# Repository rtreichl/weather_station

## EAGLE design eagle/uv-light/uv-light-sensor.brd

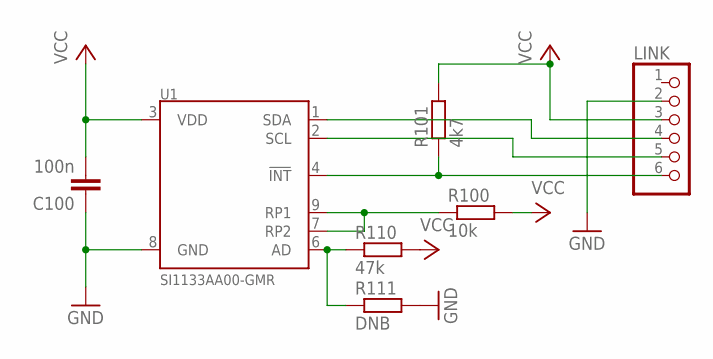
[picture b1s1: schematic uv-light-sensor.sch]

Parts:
C100: 100n; C0603
LINK: PINHD-1X6; 1X06
R100: 10k; R0603
R101: 4k7; R0603
R110: 47k; R0603
R111: DNB; R0603
U1: SI1133AA00-GMR; QFN-10/2MM

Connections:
GND: C100.1, LINK.2, R111.2, U1.8 (GND)
unnamed: LINK.6, R101.1, U1.4 (!INT)
unnamed: LINK.5, U1.2 (SCL)
unnamed: LINK.4, U1.1 (SDA)
unnamed: R100.1, U1.7 (RP2), U1.9 (RP1)
unnamed: R110.1, R111.1, U1.6 (AD)
VCC: C100.2, LINK.3, R100.2, R101.2, R110.2, U1.3 (VDD)

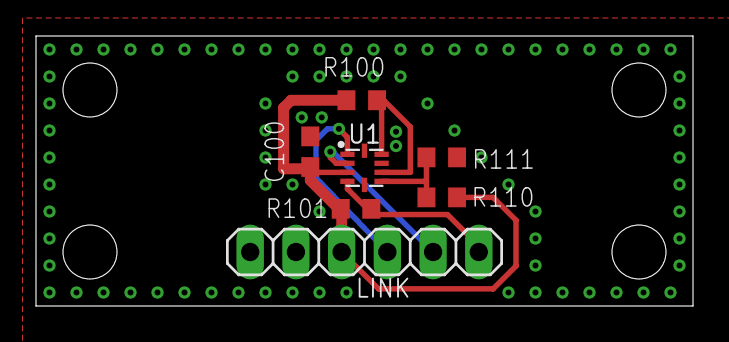
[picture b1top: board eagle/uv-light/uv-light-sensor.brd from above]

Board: 2 copper layers, 36.5 x 15.0 mm, 7 parts (0 on the bottom side), 7 nets.

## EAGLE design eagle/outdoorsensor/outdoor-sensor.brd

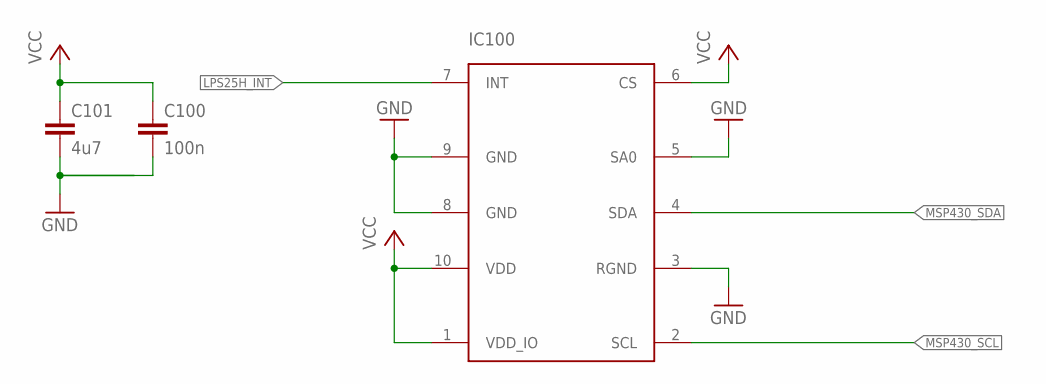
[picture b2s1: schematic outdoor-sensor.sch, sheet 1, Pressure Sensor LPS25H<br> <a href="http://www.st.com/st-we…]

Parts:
C100: 100n; C0603; MPN STP100NF04
C101: 4u7; C0603
IC100: LPS25H; MPN LPS25HBTR

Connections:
GND: C100.2, C101.2, IC100.3 (RGND), IC100.5 (SA0), IC100.8 (GND), IC100.9 (GND); also elsewhere on the board
LPS25H_INT: IC100.7 (INT); also elsewhere on the board
MSP430_SCL: IC100.2 (SCL); also elsewhere on the board
MSP430_SDA: IC100.4 (SDA); also elsewhere on the board
VCC: C100.1, C101.1, IC100.1 (VDD_IO), IC100.6 (CS), IC100.10 (VDD); also elsewhere on the board

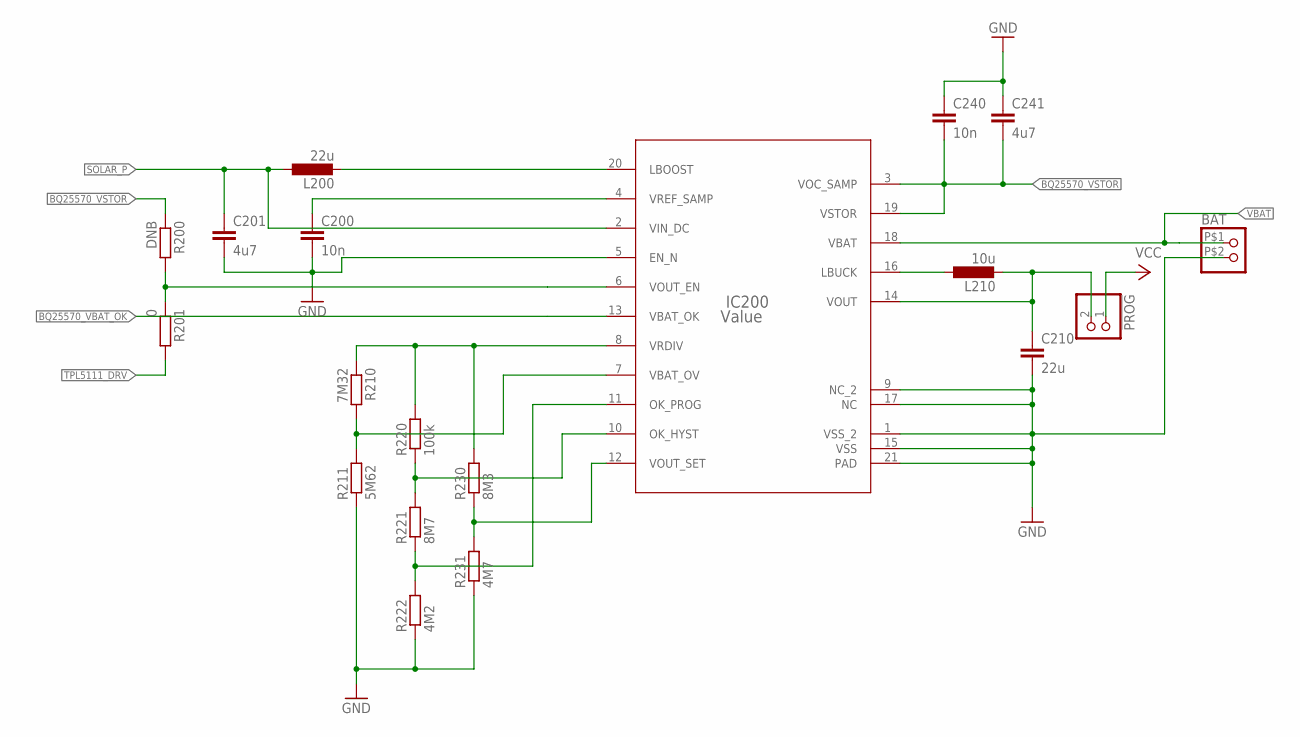
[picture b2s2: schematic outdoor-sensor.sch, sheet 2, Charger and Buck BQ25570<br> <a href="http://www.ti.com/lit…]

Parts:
!PROG: PINHD-1X2; 1X02
BAT: PINHD-1X2IPBS-102-01-T-S-GP; IPBS-102-01-T-S-GP
C200, C240: 10n; C0603
C201, C241: 4u7; C0603
C210: 22u; C0603; MPN 06034D226MAT2A
IC200: Value; RGR0020A
L200: 22u; L3944
L210: 10u; L2.5X2.0
R200: DNB; R0603
R201: 0; R0603
R210: 7M32; R0603
R211: 5M62; R0603
R220: 100k; R0603
R221: 8M7; R0603
R222: 4M2; R0603
R230: 8M3; R0603
R231: 4M7; R0603

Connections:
BQ25570_VBAT_OK: IC200.13 (VBAT_OK); also elsewhere on the board
BQ25570_VOUT_EN: IC200.6 (VOUT_EN), R200.2, R201.1
BQ25570_VSTOR: C240.2, C241.2, IC200.3 (VOC_SAMP), IC200.19 (VSTOR), R200.1; also elsewhere on the board
GND: BAT.P$2 (2), C200.2, C201.2, C210.2, C240.1, C241.1, IC200.1 (VSS_2), IC200.5 (EN_N), IC200.9 (NC_2), IC200.15 (VSS), IC200.17 (NC), IC200.21 (PAD), R211.1, R222.1, R231.1; also elsewhere on the board
unnamed: IC200.10 (OK_HYST), R220.1, R221.2
unnamed: IC200.8 (VRDIV), R210.1, R220.2, R230.2
unnamed: IC200.7 (VBAT_OV), R210.2, R211.2
unnamed: IC200.11 (OK_PROG), R221.1, R222.2
unnamed: IC200.20 (LBOOST), L200.P$2 (2)
unnamed: C200.1, IC200.4 (VREF_SAMP)
unnamed: IC200.12 (VOUT_SET), R230.1, R231.2
unnamed: !PROG.2, C210.1, IC200.14 (VOUT), L210.P$2 (2)
unnamed: IC200.16 (LBUCK), L210.P$1 (1)
SOLAR_P: C201.1, IC200.2 (VIN_DC), L200.P$1 (1); also elsewhere on the board
TPL5111_DRV: R201.2; also elsewhere on the board
VBAT: BAT.P$1 (1), IC200.18 (VBAT); also elsewhere on the board
VCC: !PROG.1; also elsewhere on the board

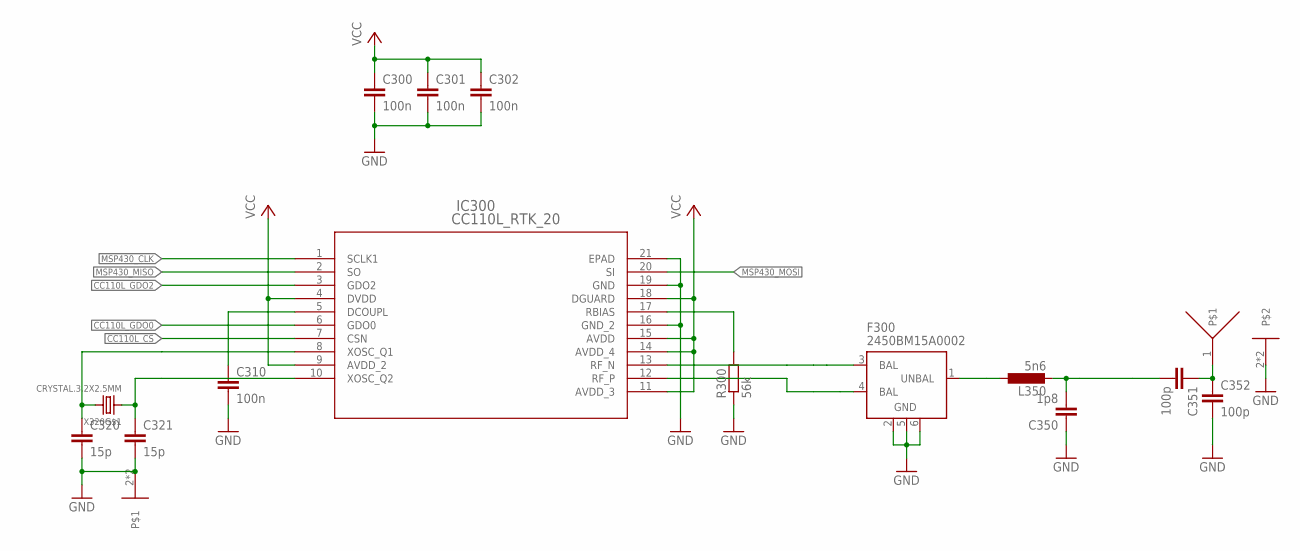
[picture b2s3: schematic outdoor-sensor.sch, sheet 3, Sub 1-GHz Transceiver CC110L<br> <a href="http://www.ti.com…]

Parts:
C300, C301, C302, C310: 100n; C0603; MPN STP100NF04
C320, C321: 15p; C0603
C350: 1p8; C0603K
C351: 100p; C0603
C352: 100p; C0603K
F300: 2450BM15A0002
IC300: CC110L_RTK_20; RTK20_2P4X2P4
L350: 5n6; L2012C
R300: 56k; R0603
U$1: ANTENNA868W3013-INV; W3013-INV
X320: CRYSTAL.3.2X2.5MM; 3.2X2.5MM

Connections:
!CC110L_CS: IC300.7 (CSN); also elsewhere on the board
CC110L_GDO0: IC300.6 (GDO0); also elsewhere on the board
CC110L_GDO2: IC300.3 (GDO2); also elsewhere on the board
GND: C300.2, C301.2, C302.2, C310.2, C320.2, C321.2, C350.1, C352.2, F300.2 (GND), F300.5 (GND), F300.6 (GND), IC300.16 (GND_2), IC300.19 (GND), IC300.21 (EPAD), R300.1, U$1.2, U$1.3, X320.2, X320.4; also elsewhere on the board
MSP430_CLK: IC300.1 (SCLK1); also elsewhere on the board
MSP430_MISO: IC300.2 (SO); also elsewhere on the board
MSP430_MOSI: IC300.20 (SI); also elsewhere on the board
unnamed: C351.1, C352.1, U$1.1
unnamed: F300.1 (UNBAL), L350.1
unnamed: C320.1, IC300.8 (XOSC_Q1), X320.3 (2)
unnamed: F300.3 (BAL), IC300.13 (RF_N)
unnamed: F300.4 (BAL), IC300.12 (RF_P)
unnamed: C350.2, C351.2, L350.2
unnamed: C310.1, IC300.5 (DCOUPL)
unnamed: IC300.17 (RBIAS), R300.2
unnamed: C321.1, IC300.10 (XOSC_Q2), X320.1
VCC: C300.1, C301.1, C302.1, IC300.4 (DVDD), IC300.9 (AVDD_2), IC300.11 (AVDD_3), IC300.14 (AVDD_4), IC300.15 (AVDD), IC300.18 (DGUARD); also elsewhere on the board

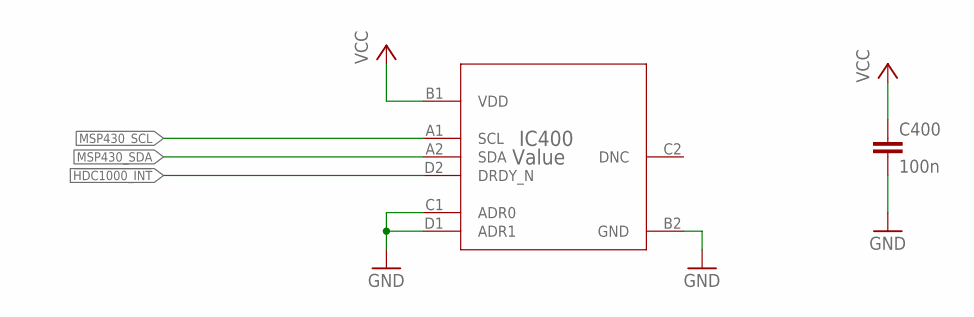
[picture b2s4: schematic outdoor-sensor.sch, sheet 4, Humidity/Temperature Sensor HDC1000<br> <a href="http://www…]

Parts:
C400: 100n; C0603; MPN STP100NF04
IC400: Value; YPA0008AGAE

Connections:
!HDC1000_INT: IC400.D2 (DRDY_N); also elsewhere on the board
GND: C400.2, IC400.B2 (GND), IC400.C1 (ADR0), IC400.D1 (ADR1); also elsewhere on the board
MSP430_SCL: IC400.A1 (SCL); also elsewhere on the board
MSP430_SDA: IC400.A2 (SDA); also elsewhere on the board
VCC: C400.1, IC400.B1 (VDD); also elsewhere on the board

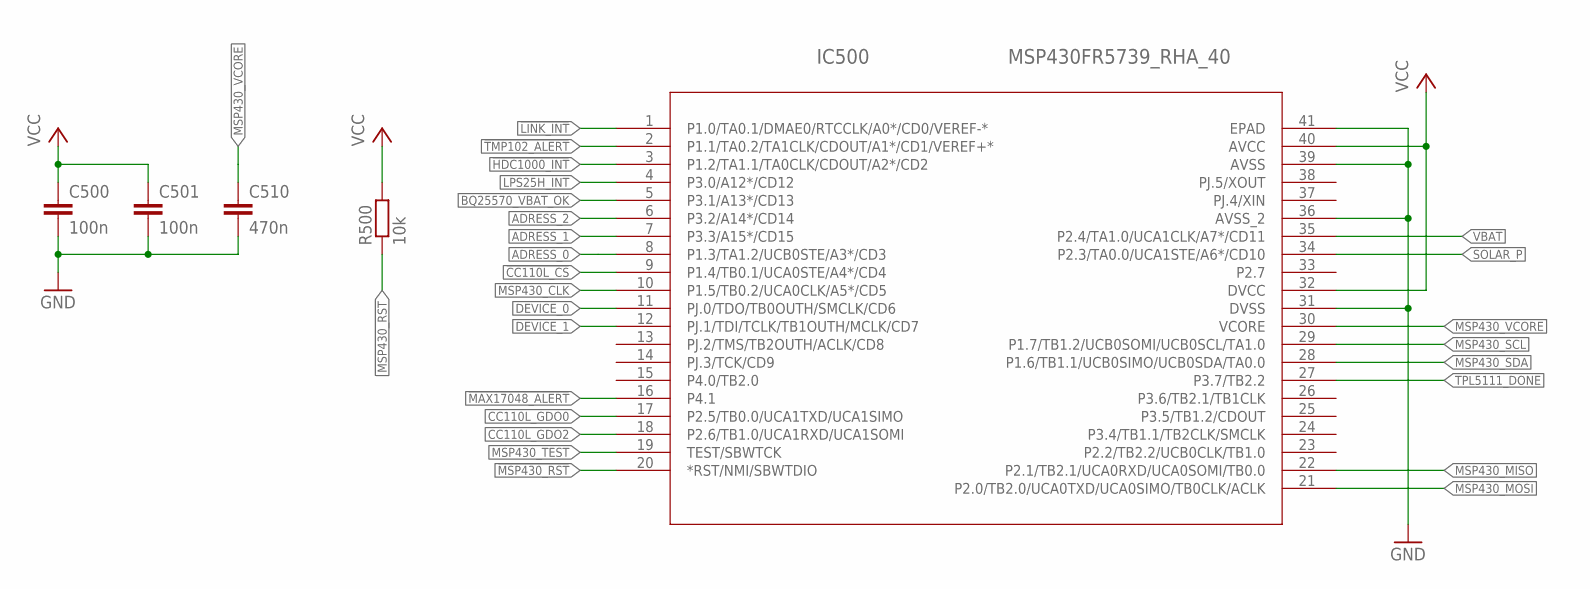
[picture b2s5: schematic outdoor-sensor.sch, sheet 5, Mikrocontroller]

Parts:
C500, C501: 100n; C0603; MPN STP100NF04
C510: 470n; C0603
IC500: MSP430FR5739_RHA_40; RHA40_2P9X2P9
R500: 10k; R0603

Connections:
!CC110L_CS: IC500.9 (P1.4/TB0.1/UCA0STE/A4*/CD4); also elsewhere on the board
!HDC1000_INT: IC500.3 (P1.2/TA1.1/TA0CLK/CDOUT/A2*/CD2); also elsewhere on the board
!LINK_INT: IC500.1 (P1.0/TA0.1/DMAE0/RTCCLK/A0*/CD0/VEREF-*); also elsewhere on the board
!MAX17048_ALERT: IC500.16 (P4.1); also elsewhere on the board
!MSP430_RST: IC500.20 (*RST/NMI/SBWTDIO), R500.1; also elsewhere on the board
!TMP102_ALERT: IC500.2 (P1.1/TA0.2/TA1CLK/CDOUT/A1*/CD1/VEREF+*); also elsewhere on the board
ADRESS_0: IC500.8 (P1.3/TA1.2/UCB0STE/A3*/CD3); also elsewhere on the board
ADRESS_1: IC500.7 (P3.3/A15*/CD15); also elsewhere on the board
ADRESS_2: IC500.6 (P3.2/A14*/CD14); also elsewhere on the board
BQ25570_VBAT_OK: IC500.5 (P3.1/A13*/CD13); also elsewhere on the board
CC110L_GDO0: IC500.17 (P2.5/TB0.0/UCA1TXD/UCA1SIMO); also elsewhere on the board
CC110L_GDO2: IC500.18 (P2.6/TB1.0/UCA1RXD/UCA1SOMI); also elsewhere on the board
DEVICE_0: IC500.11 (PJ.0/TDO/TB0OUTH/SMCLK/CD6); also elsewhere on the board
DEVICE_1: IC500.12 (PJ.1/TDI/TCLK/TB1OUTH/MCLK/CD7); also elsewhere on the board
GND: C500.2, C501.2, C510.2, IC500.31 (DVSS), IC500.36 (AVSS_2), IC500.39 (AVSS), IC500.41 (EPAD); also elsewhere on the board
LPS25H_INT: IC500.4 (P3.0/A12*/CD12); also elsewhere on the board
MSP430_CLK: IC500.10 (P1.5/TB0.2/UCA0CLK/A5*/CD5); also elsewhere on the board
MSP430_MISO: IC500.22 (P2.1/TB2.1/UCA0RXD/UCA0SOMI/TB0.0); also elsewhere on the board
MSP430_MOSI: IC500.21 (P2.0/TB2.0/UCA0TXD/UCA0SIMO/TB0CLK/ACLK); also elsewhere on the board
MSP430_SCL: IC500.29 (P1.7/TB1.2/UCB0SOMI/UCB0SCL/TA1.0); also elsewhere on the board
MSP430_SDA: IC500.28 (P1.6/TB1.1/UCB0SIMO/UCB0SDA/TA0.0); also elsewhere on the board
MSP430_TEST: IC500.19 (TEST/SBWTCK); also elsewhere on the board
MSP430_VCORE: C510.1, IC500.30 (VCORE)
SOLAR_P: IC500.34 (P2.3/TA0.0/UCA1STE/A6*/CD10); also elsewhere on the board
TPL5111_DONE: IC500.27 (P3.7/TB2.2); also elsewhere on the board
VBAT: IC500.35 (P2.4/TA1.0/UCA1CLK/A7*/CD11); also elsewhere on the board
VCC: C500.1, C501.1, IC500.32 (DVCC), IC500.40 (AVCC), R500.2; also elsewhere on the board

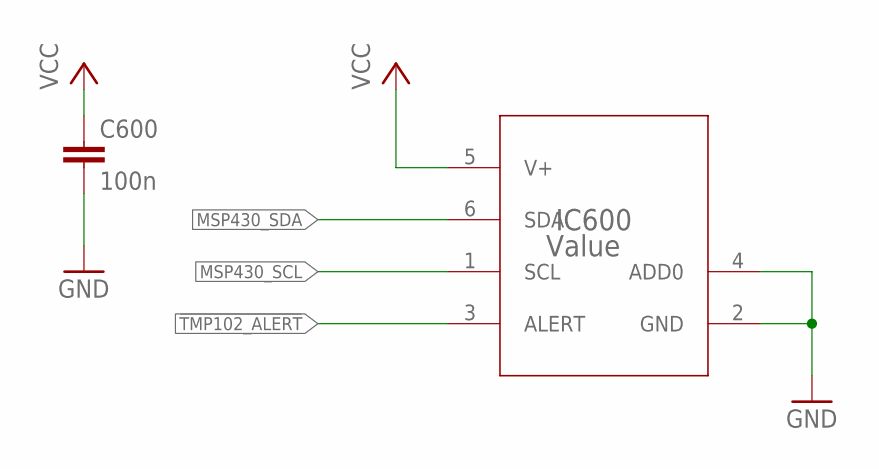
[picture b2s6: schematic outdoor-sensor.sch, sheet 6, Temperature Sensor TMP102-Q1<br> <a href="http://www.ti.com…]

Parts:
C600: 100n; C0603; MPN STP100NF04
IC600: Value; DRL0006A

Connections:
!TMP102_ALERT: IC600.3 (ALERT); also elsewhere on the board
GND: C600.2, IC600.2 (GND), IC600.4 (ADD0); also elsewhere on the board
MSP430_SCL: IC600.1 (SCL); also elsewhere on the board
MSP430_SDA: IC600.6 (SDA); also elsewhere on the board
VCC: C600.1, IC600.5 (V+); also elsewhere on the board

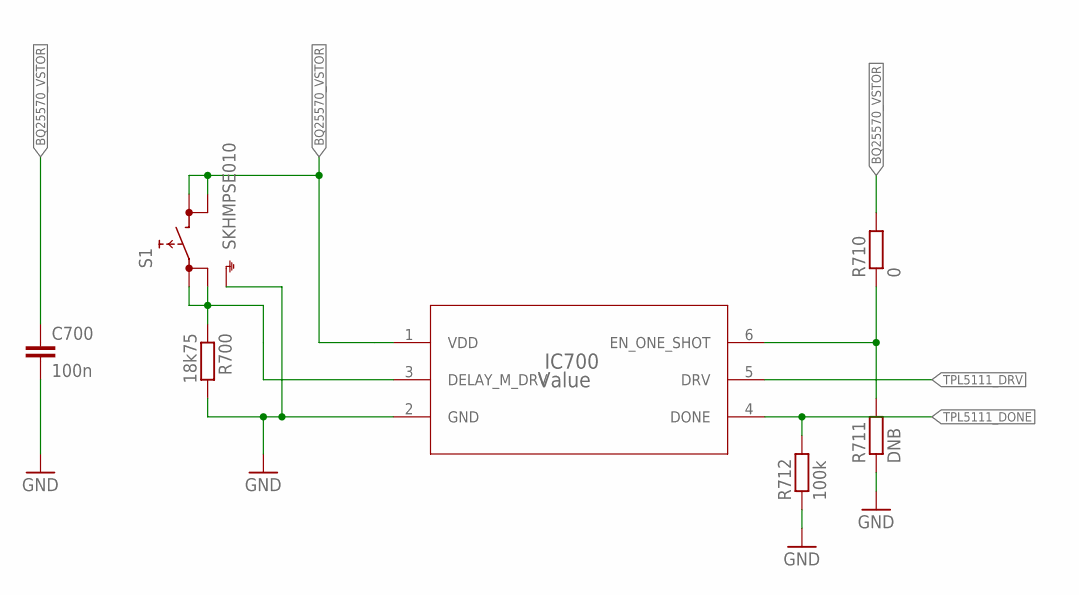
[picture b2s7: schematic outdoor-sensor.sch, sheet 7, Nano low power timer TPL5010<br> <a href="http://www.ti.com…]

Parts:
C700: 100n; C0603; MPN STP100NF04
IC700: Value; DDC0006A_N
R700: 18k75; R0603
R710: 0; R0603
R711: DNB; R0603
R712: 100k; R0603
S1: SKHMPSE010; SKHMPXE010

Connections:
BQ25570_VSTOR: C700.1, IC700.1 (VDD), R710.2, S1.3 (2.1), S1.4 (2.2); also elsewhere on the board
GND: C700.2, IC700.2 (GND), R700.2, R711.1, R712.1, S1.5 (SH); also elsewhere on the board
unnamed: IC700.3 (DELAY_M_DRV), R700.1, S1.1 (1.1), S1.2 (1.2)
TPL5010_RST_N: IC700.6 (EN_ONE_SHOT), R710.1, R711.2
TPL5111_DONE: IC700.4 (DONE), R712.2; also elsewhere on the board
TPL5111_DRV: IC700.5 (DRV); also elsewhere on the board

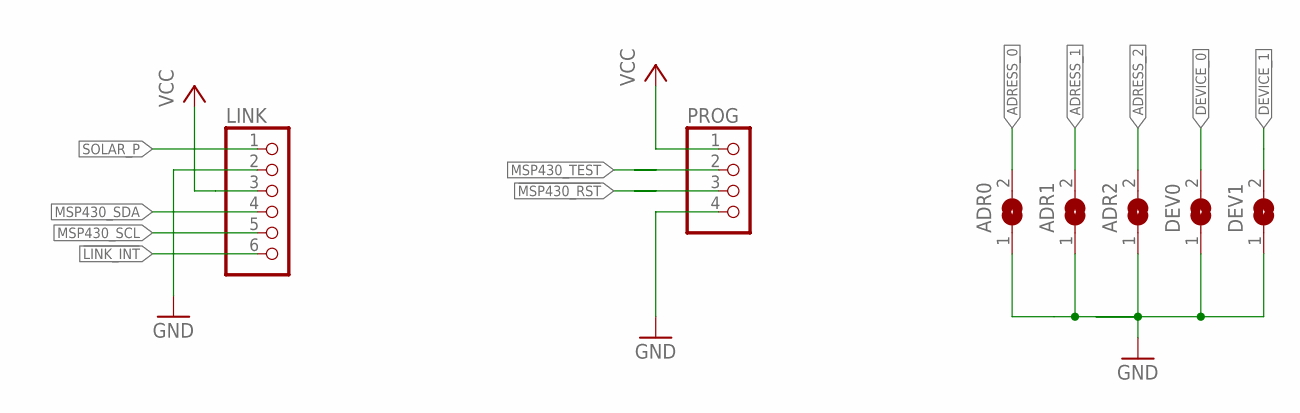
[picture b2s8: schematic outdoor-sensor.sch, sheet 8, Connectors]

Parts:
ADR0, ADR1, ADR2: SJW
DEV0, DEV1: SJW
LINK: PINHD-1X6; 1X06
PROG: PINHD-1X4; 1X04

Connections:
!LINK_INT: LINK.6; also elsewhere on the board
!MSP430_RST: PROG.3; also elsewhere on the board
ADRESS_0: ADR0.2; also elsewhere on the board
ADRESS_1: ADR1.2; also elsewhere on the board
ADRESS_2: ADR2.2; also elsewhere on the board
DEVICE_0: DEV0.2; also elsewhere on the board
DEVICE_1: DEV1.2; also elsewhere on the board
GND: ADR0.1, ADR1.1, ADR2.1, DEV0.1, DEV1.1, LINK.2, PROG.4; also elsewhere on the board
MSP430_SCL: LINK.5; also elsewhere on the board
MSP430_SDA: LINK.4; also elsewhere on the board
MSP430_TEST: PROG.2; also elsewhere on the board
SOLAR_P: LINK.1; also elsewhere on the board
VCC: LINK.3, PROG.1; also elsewhere on the board

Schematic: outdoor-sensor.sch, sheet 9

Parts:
C800: 100n; C0603
IC800: MAX17048X+; 21-0555B_W80B1-1

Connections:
!MAX17048_ALERT: IC800.B4 (*ALRT); also elsewhere on the board
GND: C800.2, IC800.A1 (CTG), IC800.A4 (GND), IC800.B3 (QSTRT); also elsewhere on the board
MSP430_SCL: IC800.B2 (SCL); also elsewhere on the board
MSP430_SDA: IC800.B1 (SDA); also elsewhere on the board
VBAT: C800.1, IC800.A2 (CELL), IC800.A3 (VDD); also elsewhere on the board

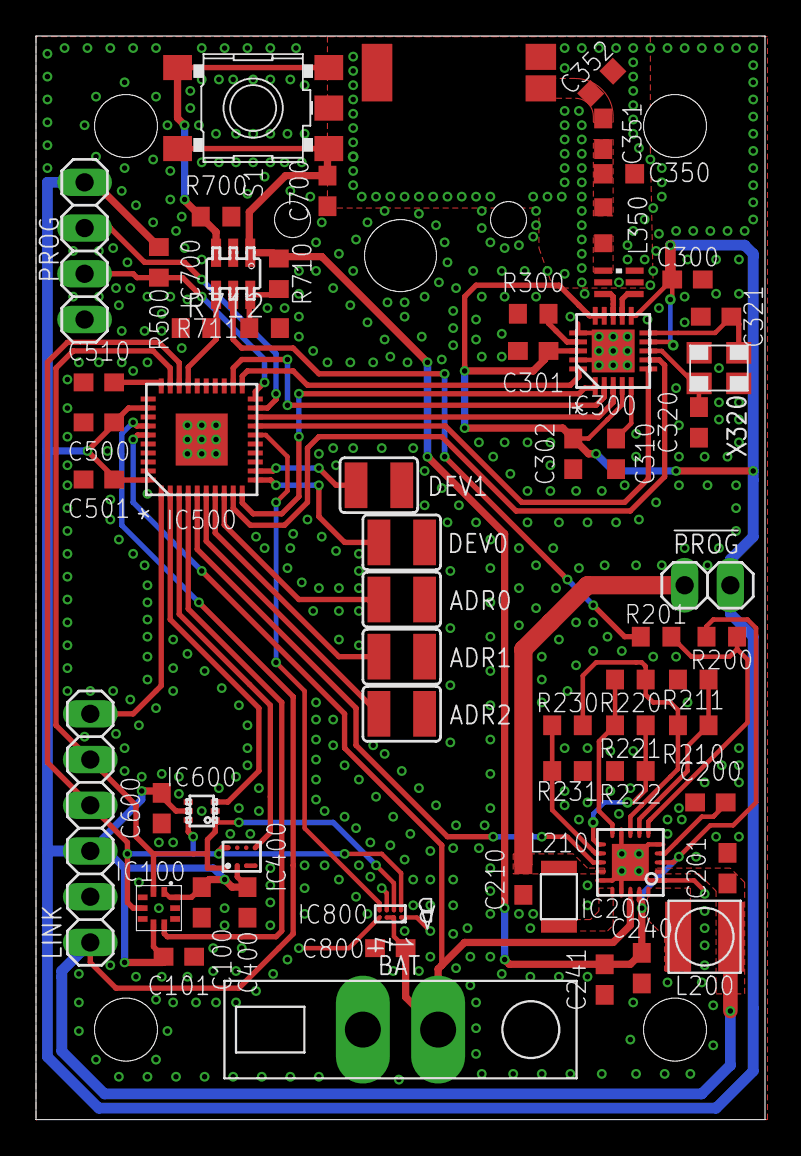
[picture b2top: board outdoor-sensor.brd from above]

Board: 2 copper layers, 40.5 x 60.2 mm, 62 parts (0 on the bottom side), 50 nets.

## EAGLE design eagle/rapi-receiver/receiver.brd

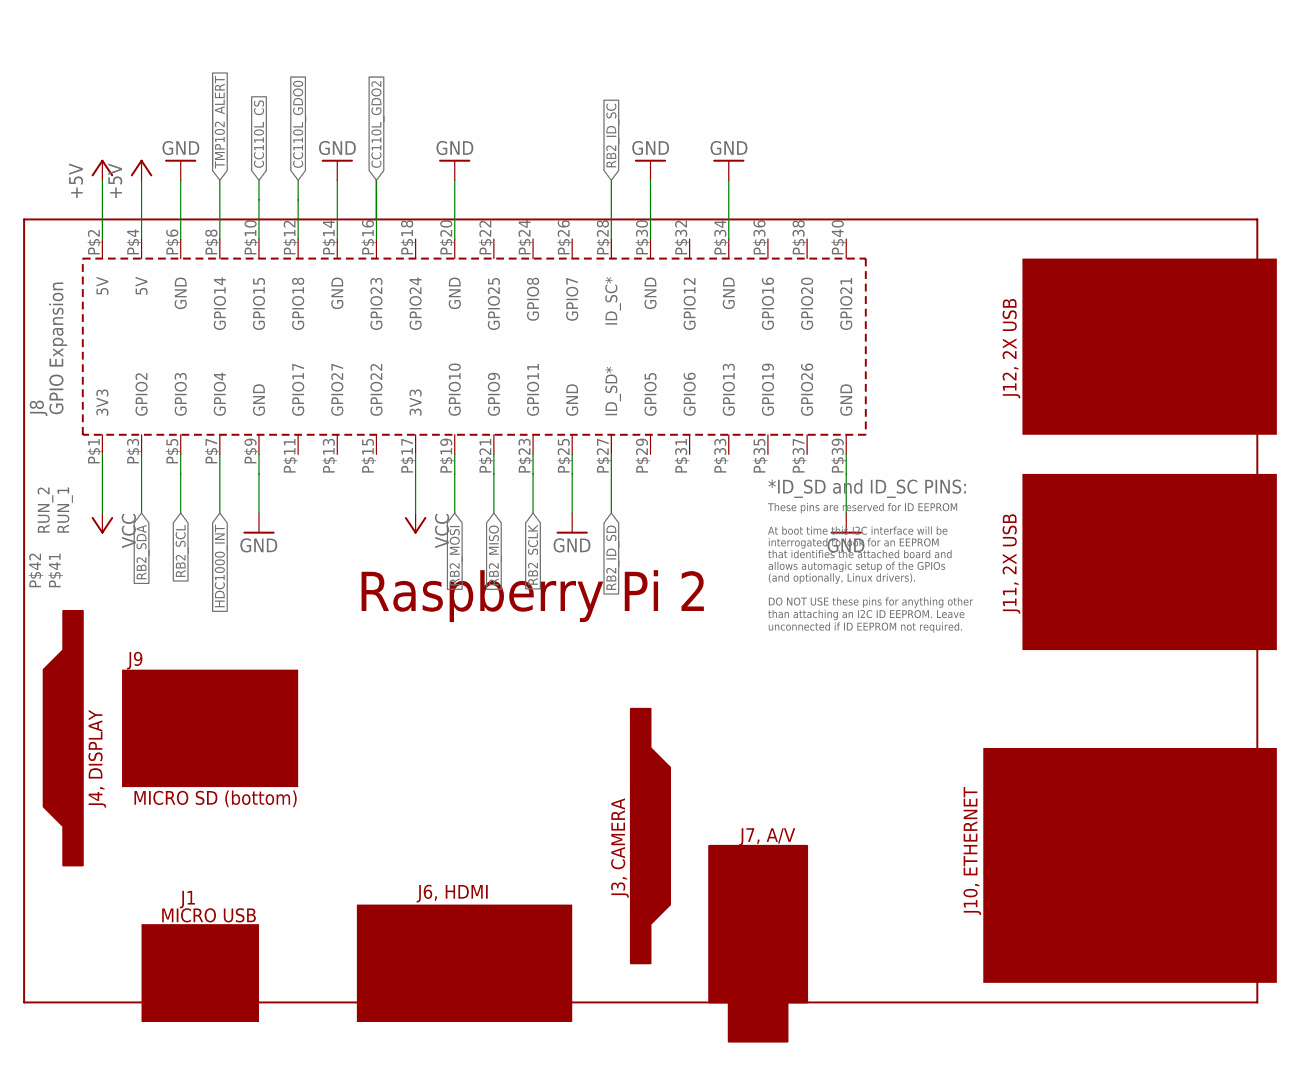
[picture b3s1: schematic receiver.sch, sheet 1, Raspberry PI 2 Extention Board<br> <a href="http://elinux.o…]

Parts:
PCB1: RPI2

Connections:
!HDC1000_INT: PCB1.P$7 (GPIO4); also elsewhere on the board
!TMP102_ALERT: PCB1.P$8 (GPIO14); also elsewhere on the board
+5V: PCB1.P$2 (5V), PCB1.P$4 (5V)
CC110L_CS: PCB1.P$10 (GPIO15); also elsewhere on the board
CC110L_GDO0: PCB1.P$12 (GPIO18); also elsewhere on the board
CC110L_GDO2: PCB1.P$16 (GPIO23); also elsewhere on the board
GND: PCB1.P$6 (GND), PCB1.P$9 (GND), PCB1.P$14 (GND), PCB1.P$20 (GND), PCB1.P$25 (GND), PCB1.P$30 (GND), PCB1.P$34 (GND), PCB1.P$39 (GND); also elsewhere on the board
RB2_ID_SC: PCB1.P$28 (ID_SC*); also elsewhere on the board
RB2_ID_SD: PCB1.P$27 (ID_SD*); also elsewhere on the board
RB2_MISO: PCB1.P$21 (GPIO9); also elsewhere on the board
RB2_MOSI: PCB1.P$19 (GPIO10); also elsewhere on the board
RB2_SCL: PCB1.P$5 (GPIO3); also elsewhere on the board
RB2_SCLK: PCB1.P$23 (GPIO11); also elsewhere on the board
RB2_SDA: PCB1.P$3 (GPIO2); also elsewhere on the board
VCC: PCB1.P$1 (3V3), PCB1.P$17 (3V3); also elsewhere on the board

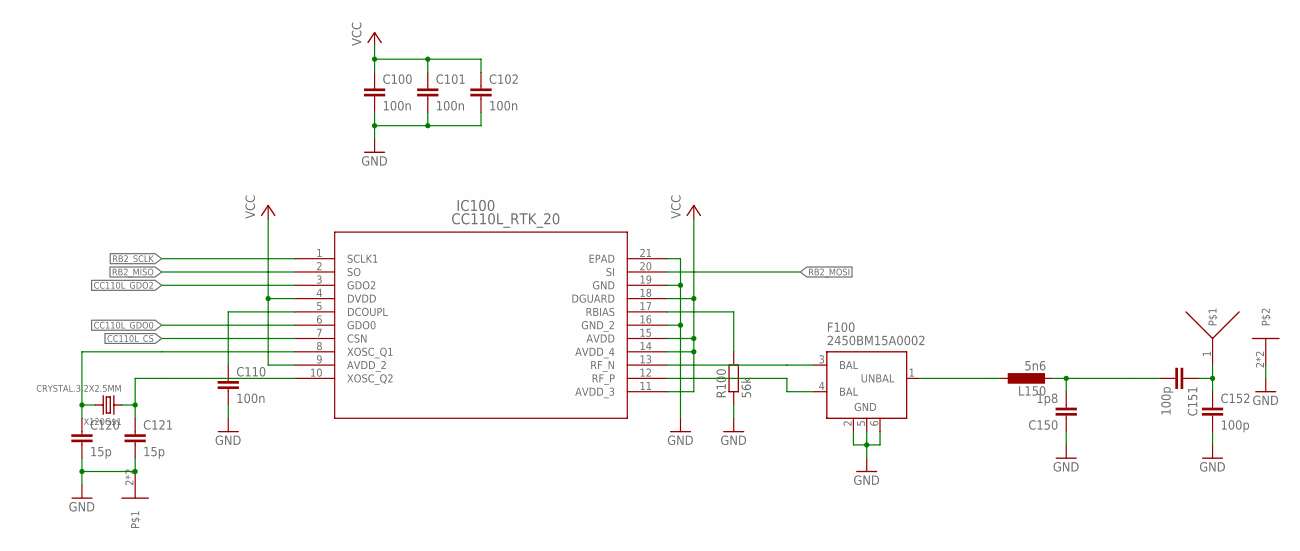
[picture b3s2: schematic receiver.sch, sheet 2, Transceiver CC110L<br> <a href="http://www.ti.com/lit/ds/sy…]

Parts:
C100, C101, C102, C110: 100n; C0603
C120, C121: 15p; C0603
C150: 1p8; C0603K
C151: 100p; C0603
C152: 100p; C0603K
F100: 2450BM15A0002
IC100: CC110L_RTK_20; RTK20_2P4X2P4
L150: 5n6; L2012C
R100: 56k; R0603
U$1: ANTENNA868W3013-INV; W3013-INV
X120: CRYSTAL.3.2X2.5MM; 3.2X2.5MM

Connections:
CC110L_CS: IC100.7 (CSN); also elsewhere on the board
CC110L_GDO0: IC100.6 (GDO0); also elsewhere on the board
CC110L_GDO2: IC100.3 (GDO2); also elsewhere on the board
GND: C100.2, C101.2, C102.2, C110.2, C120.2, C121.2, C150.1, C152.2, F100.2 (GND), F100.5 (GND), F100.6 (GND), IC100.16 (GND_2), IC100.19 (GND), IC100.21 (EPAD), R100.1, U$1.2, U$1.3, X120.2, X120.4; also elsewhere on the board
unnamed: C151.1, C152.1, U$1.1
unnamed: C120.1, IC100.8 (XOSC_Q1), X120.3 (2)
unnamed: F100.1 (UNBAL), L150.1
unnamed: F100.3 (BAL), IC100.13 (RF_N)
unnamed: F100.4 (BAL), IC100.12 (RF_P)
unnamed: C150.2, C151.2, L150.2
unnamed: C110.1, IC100.5 (DCOUPL)
unnamed: IC100.17 (RBIAS), R100.2
unnamed: C121.1, IC100.10 (XOSC_Q2), X120.1
RB2_MISO: IC100.2 (SO); also elsewhere on the board
RB2_MOSI: IC100.20 (SI); also elsewhere on the board
RB2_SCLK: IC100.1 (SCLK1); also elsewhere on the board
VCC: C100.1, C101.1, C102.1, IC100.4 (DVDD), IC100.9 (AVDD_2), IC100.11 (AVDD_3), IC100.14 (AVDD_4), IC100.15 (AVDD), IC100.18 (DGUARD); also elsewhere on the board

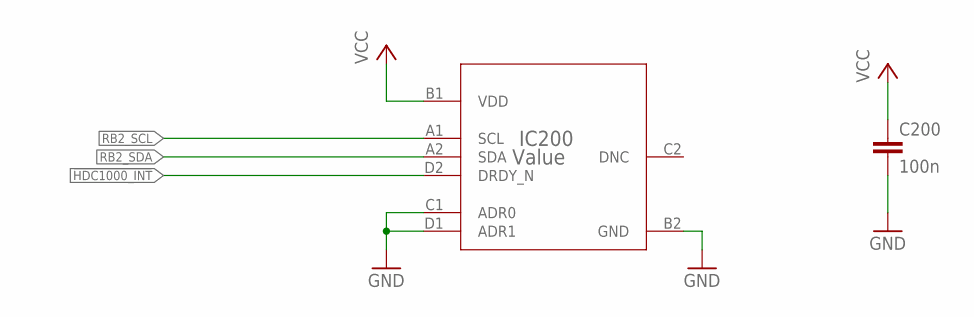
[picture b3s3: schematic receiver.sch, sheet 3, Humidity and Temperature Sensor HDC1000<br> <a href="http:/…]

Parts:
C200: 100n; C0603
IC200: Value; YPA0008AGAE

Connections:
!HDC1000_INT: IC200.D2 (DRDY_N); also elsewhere on the board
GND: C200.2, IC200.B2 (GND), IC200.C1 (ADR0), IC200.D1 (ADR1); also elsewhere on the board
RB2_SCL: IC200.A1 (SCL); also elsewhere on the board
RB2_SDA: IC200.A2 (SDA); also elsewhere on the board
VCC: C200.1, IC200.B1 (VDD); also elsewhere on the board

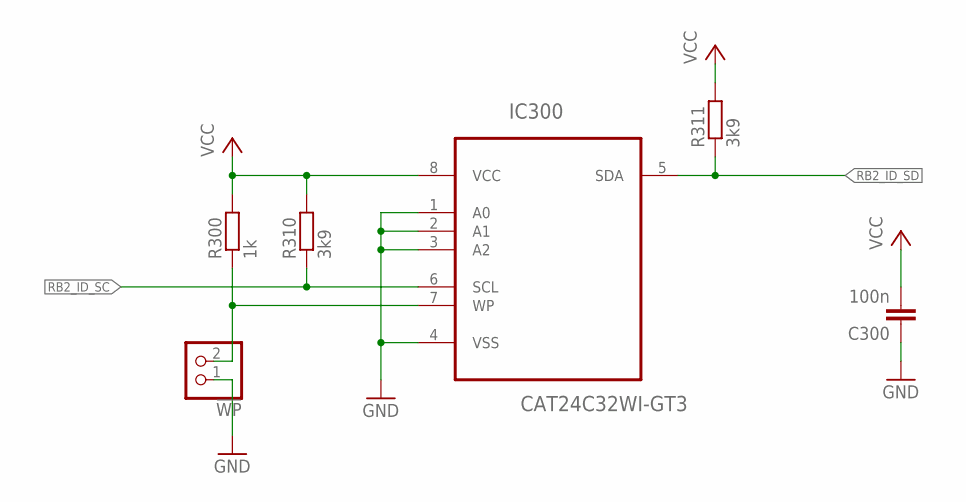
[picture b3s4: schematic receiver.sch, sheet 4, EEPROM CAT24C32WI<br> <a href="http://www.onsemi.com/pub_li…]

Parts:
!WP: PINHD-1X2; 1X02
C300: 100n; C0603
IC300: CAT24C32WI-GT3; SOIC127P600X175-8N
R300: 1k; R0603
R310, R311: 3k9; R0603

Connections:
GND: !WP.1, C300.1, IC300.1 (A0), IC300.2 (A1), IC300.3 (A2), IC300.4 (VSS); also elsewhere on the board
unnamed: !WP.2, IC300.7 (WP), R300.1
RB2_ID_SC: IC300.6 (SCL), R310.1; also elsewhere on the board
RB2_ID_SD: IC300.5 (SDA), R311.1; also elsewhere on the board
VCC: C300.2, IC300.8 (VCC), R300.2, R310.2, R311.2; also elsewhere on the board

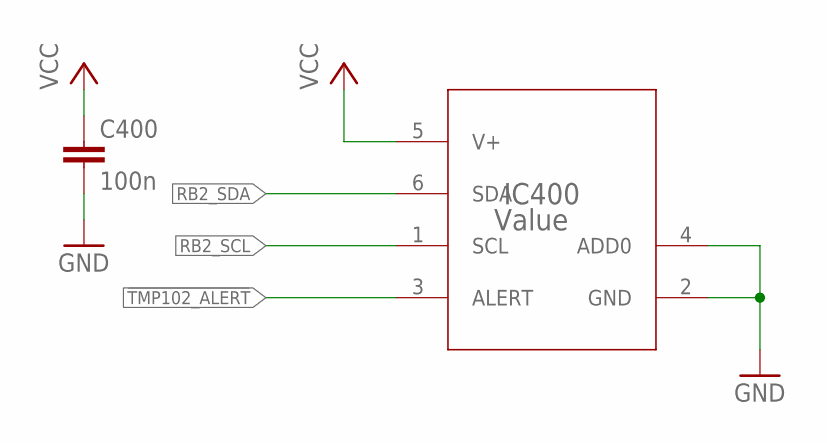
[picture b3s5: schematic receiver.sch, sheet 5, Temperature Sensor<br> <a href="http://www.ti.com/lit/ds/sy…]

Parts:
C400: 100n; C0603
IC400: Value; DRL0006A

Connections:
!TMP102_ALERT: IC400.3 (ALERT); also elsewhere on the board
GND: C400.2, IC400.2 (GND), IC400.4 (ADD0); also elsewhere on the board
RB2_SCL: IC400.1 (SCL); also elsewhere on the board
RB2_SDA: IC400.6 (SDA); also elsewhere on the board
VCC: C400.1, IC400.5 (V+); also elsewhere on the board

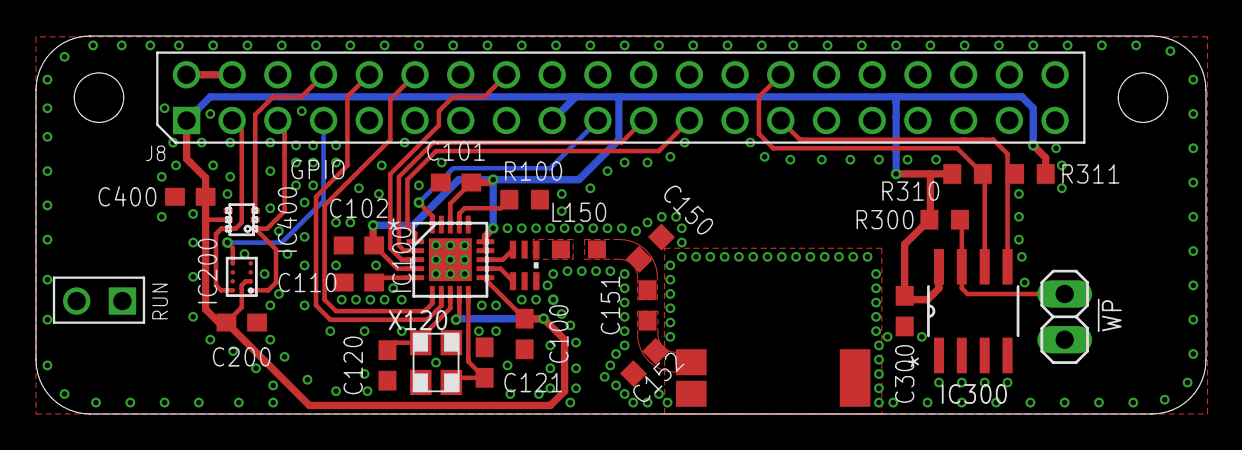
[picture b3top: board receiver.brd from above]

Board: 2 copper layers, 65.0 x 21.0 mm, 26 parts (0 on the bottom side), 25 nets.

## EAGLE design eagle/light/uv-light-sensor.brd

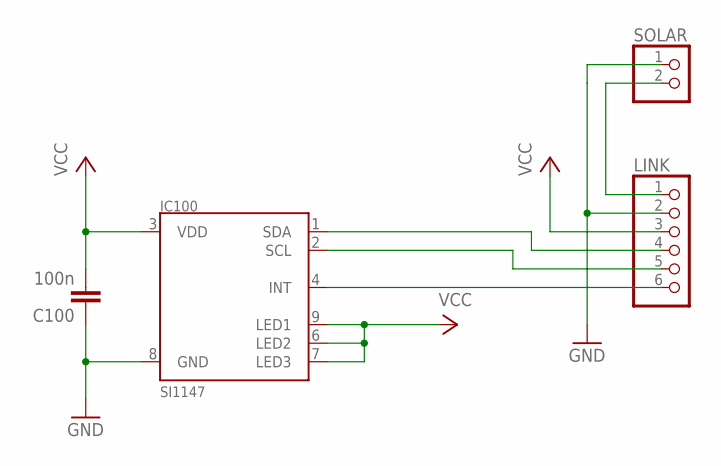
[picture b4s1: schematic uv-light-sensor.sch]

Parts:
C100: 100n; C0603
IC100: SI1147; QFN-10/2MM
LINK: PINHD-1X6; 1X06
SOLAR: PINHD-1X2; 1X02

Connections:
GND: C100.1, IC100.8 (GND), LINK.2, SOLAR.1
unnamed: IC100.4 (INT), LINK.6
unnamed: IC100.2 (SCL), LINK.5
unnamed: IC100.1 (SDA), LINK.4
unnamed: LINK.1, SOLAR.2
VCC: C100.2, IC100.3 (VDD), IC100.6 (LED2), IC100.7 (LED3), IC100.9 (LED1), LINK.3

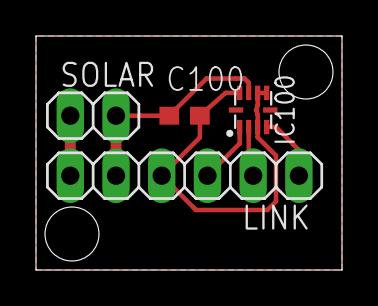
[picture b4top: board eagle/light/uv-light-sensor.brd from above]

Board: 2 copper layers, 17.0 x 13.0 mm, 4 parts (0 on the bottom side), 6 nets.

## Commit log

2015-07-07 Init: Initial commint with needed folder structur
2015-08-13 ADD: Schematics and layout for outdoor light sensor and receiver for raspberry pi 2
2015-10-21 ADD: first C-Project of transmitter
2015-10-21 CHG: updated lib, schematics and boards
2016-01-28 RM: Deleted old Prject
2016-01-28 ADD: New project for OutdoorSensor
    actually state is working
2016-01-28 CHG: Updated schematics and layout
2016-01-28 ADD: New project for Receiver on Raspbery Pi2
2016-01-28 CHG: Several changes due to new protocol
2016-01-28 CHG: added factors for conversion of raw data to real data
2016-01-28 CHG: restructed mysql commands due to protcocl changes
2016-01-28 CHG: Some structur improvments
2016-02-17 CHG: Removed extern_interrupt_handler and replaced with with new gpio interface
2016-02-17 CHG: Added new timer interface
2016-02-17 CHG: Updated some MYSQL strings
2016-02-17 CHG: reworked database data handling and added rssi for database insert
2016-02-17 FIX: fixed some bugs on cc110l driver
2016-02-18 ADD: added clock interface
2016-02-26 ADD: Added a Systemtimer function, also moved system relevant files to a own folder on the lib path renamed some macros and function due to new folder structure
2016-02-26 FIX: Moved config from ram to rom
2016-02-26 ADD: added a onewire driver. Port and Pin are selectable
2016-02-26 CHG: Improved timer driver and fixed some bugs
2016-02-26 ADD: Added an check slave function to i2c for checking availability
2016-02-26 ADD: Added driver for DS18B20 Temp. sensor
2016-02-26 FIX: fixed a bug with GPIO ISR
2016-02-26 CHG: Added library to include pathes, and cleaned up main due to fewer changes
2016-02-26 ADD: Added files for driver lib. Driver lib will be moved out of this repo. to a independently one
2016-02-29 CHG: Moved files in new directory and changed code for new structure
2016-02-29 ADD: added a i2c_slave_check function to prove if the slave exists
2016-02-29 CHG: tmp102 changed converstion rate from 1s to 125ms and added a wait statement for it
2016-02-29 CHG: Splitted PA-Table marco in to different macros
2016-02-29 ADD: added a start up wait condition for the hdc1000
2016-02-29 ADD: added a start up wait condition for the si1147
2016-02-29 ADD: added an application with a new folder, which contains the application code
2016-02-29 CHG: SPI clock divider is now 2 instead of 4
2016-05-07 ADD: First Version of Webinterface
2016-05-07 CHG: reworked some timings
2016-05-07 CHG: reworked Raspi Code
2016-05-07 CHG: fixed some issuses on pcb
2016-05-07 FIX: fixed some problems on libary
2016-05-07 CHG: changed drivers to gcc
2016-05-07 FIX: fixed problems with gcc
2016-05-16 CLEAN: Moved some code to a new files
    Moved Debug code to his own file
    Moved Register Structs and Defines to his own file
2016-05-16 CHG: Replaced Si1147 through Si1133
2016-06-03 Add PCB Image
